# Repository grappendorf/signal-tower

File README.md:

# Signal Tower

Signal towers (or stack lights) are usually used in industrial manufacturing and display the
state of a machine to the operators. They are mounted on a pole, which makes it easy to spot a
malfunctioning machine from far away. Different colors can be used to display various conditions
(for example green = normal, red = malfunction, yellow = warning, blue = good, but low on raw
materials).

Nowadays software development is also partly regarded as an industrial process. For example
continuous integration and deployment can be fully automated. When a developer pushes new code into
the central repository, this code can be automatically build, tested and deployed onto production
servers. Testing is an essential part of this process, since you don't want bad code to creep into
production.

A fast feedback of these problems to the developers helps them to quickly react accordingly. So
today more and more development teams are installing some kind of easily perceptible
good/broken-indicators. This can either be a big monitor which displays some kind of a build
status dashboard, or a stylish industrial signal tower like the one in the picture above.

This a custom shield for an Arduino which can control three signal tower lights. It is accessable
via WLAN and the firmware implements a small HTTP server, which allows you to control the signal
tower through some simple HTTP-REST-APIs.

[Read more about this project on my website...](http://www.grappendorf.net/projects/signal-tower.html)

# Build

This project is powered by [PlatformIO](http://platformio.org/#!/)

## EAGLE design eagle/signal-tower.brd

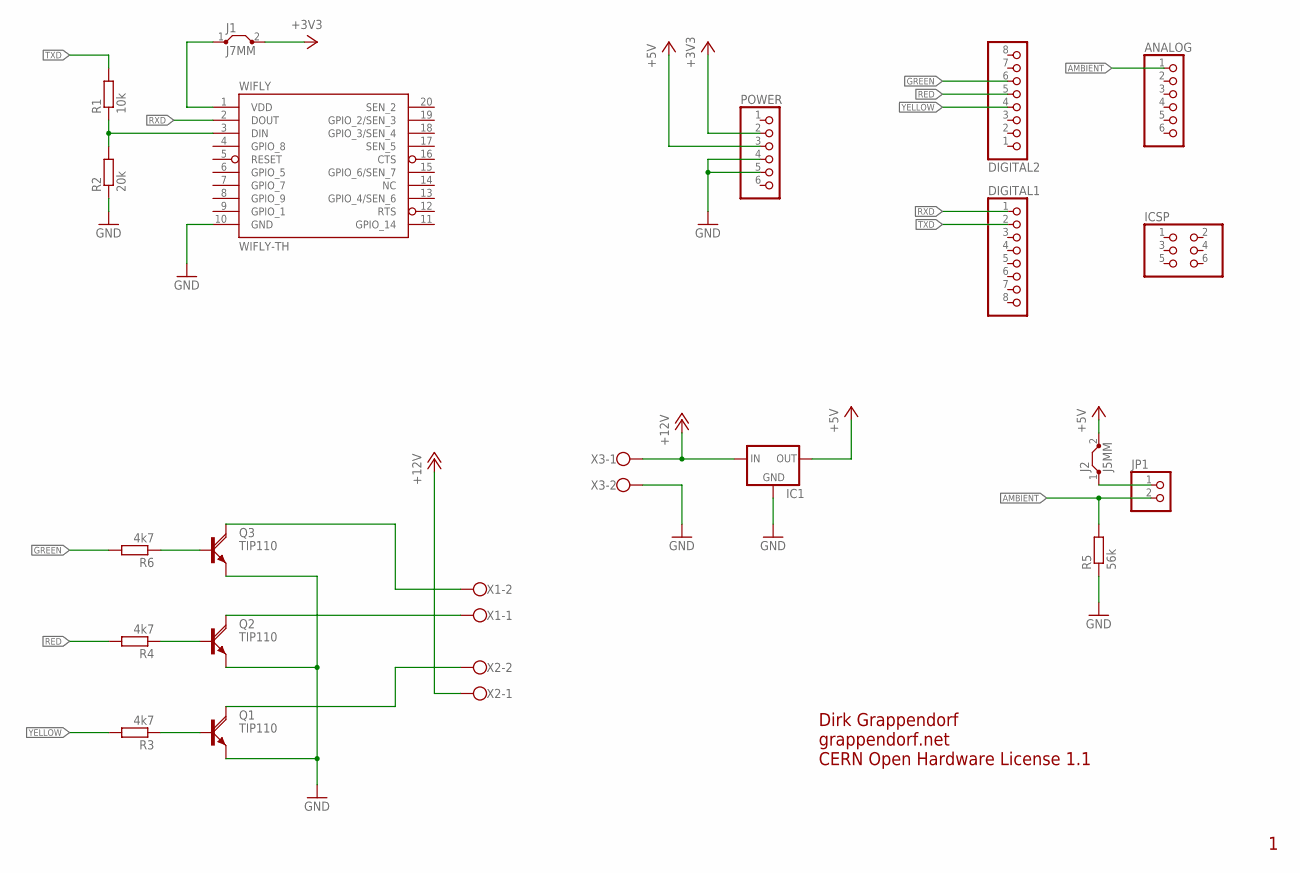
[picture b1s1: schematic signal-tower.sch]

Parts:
ANALOG: PINHD-1X6; 1X06
DIGITAL1: PINHD-1X8TH; 1X08-TH
DIGITAL2: PINHD-1X8_2.54; 1X08
IC1: 78XXS
ICSP: PINHD-2X3; 2X03
J1: J7MM; 07
J2: J5MM; 05
JP1: PINHD-1X2; 1X02
POWER: PINHD-1X6_2.54; 1X06
Q1, Q2, Q3: TIP110; TO220BV
R1: 10k; 0204/7
R2: 20k; 0204/7
R3, R4, R6: 4k7; 0204/7
R5: 56k; 0204/7
WIFLY: WIFLY-TH
X1, X2, X3: W237-102

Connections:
+3V3: J1.2, POWER.2
+5V: IC1.OUT, J2.2, POWER.3
+12V: IC1.IN, X2.1, X3.1
AMBIENT: ANALOG.1, JP1.2, R5.2
GND: IC1.GND, POWER.4, POWER.5, Q1.S (E), Q2.S (E), Q3.S (E), R2.1, R5.1, WIFLY.10 (GND), X3.2
GREEN: DIGITAL2.6, R6.2
unnamed: R1.1, R2.2, WIFLY.3 (DIN)
unnamed: Q3.D (C), X1.2
unnamed: J1.1, WIFLY.1 (VDD)
unnamed: Q1.G (B), R3.1
unnamed: Q2.G (B), R4.1
unnamed: Q3.G (B), R6.1
unnamed: Q2.D (C), X1.1
unnamed: Q1.D (C), X2.2
unnamed: J2.1, JP1.1
RED: DIGITAL2.5, R4.2
RXD: DIGITAL1.1, WIFLY.2 (DOUT)
TXD: DIGITAL1.2, R1.2
YELLOW: DIGITAL2.4, R3.2

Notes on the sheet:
Dirk Grappendorf
grappendorf.net
CERN Open Hardware License 1.1

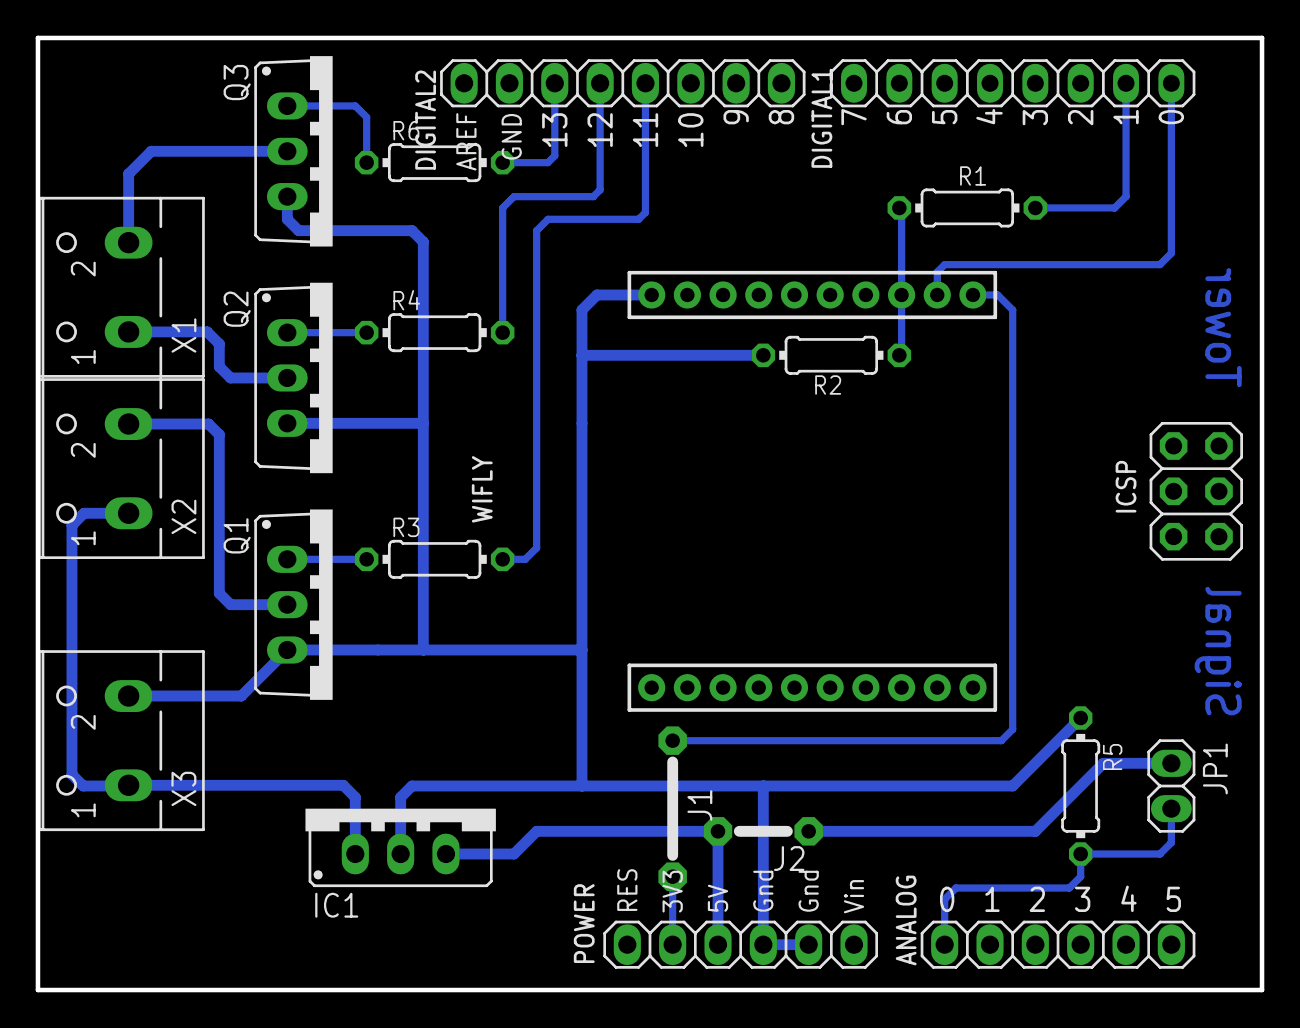
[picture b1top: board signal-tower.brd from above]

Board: 2 copper layers, 68.6 x 53.3 mm, 22 parts (0 on the bottom side), 19 nets.

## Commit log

2016-02-13 docs: add README
2016-02-13 docs: update file header
2016-02-23 convert to a PlatformIO project
2016-02-23 fix include
2016-02-23 feat: clients can specify a duration for switched on leds
2016-02-23 chore: remove no longer used cmake file
